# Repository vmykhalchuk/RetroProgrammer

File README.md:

### Ever wondered what happens when my DIY MCU based device:
* after a years of fruitfull work, something bad happens to MCU?
* or this device gets into hands of other DIY electrician for repairing?
- How then shell I find the binary of firmware used in this particular device?
- Is it located on my hard-drive, or on some of backup CDs, or ... baby elephant know where?
- What if I have many devices or single device with many MCUs, each requiring own firmware?
* Now I have to:
 - find required binaries
 - find proper software to upload it over my Programmer
 - make sure MCU model is same, and proper version of firmware is selected

Well, if this ever bothered you - then Retro Programmer is right for you!

## RetroProgrammer
Board for Arduino Nano to convert Arduino into handheld programmer (SD card support, Target IDentification, no PC required, easy to repeat, cheap)

### Idea behind Retro Programmer
 # Short: You want your DIY project to be repairable by any electrician, without skills in MCUs and deep knowledge of your device? Then Retro Programmer is for you!

 # Long story:
You have this device which you will share with others, or make it for your firends or family.
Still you are wandering, what would they do, if it gets broken, MCU in the device sets on fire or anything else happens that will require MCU to be replaced and firmware uploaded?
Without your help - this device is beyound repair, and your friends cannot just ask any electrician to repair it without having skills uploading frimware to your device.

However there is a solution - meet Retro Programmer!

This super-powerefull and low-cost solution will make it super-easy to upload firmware to your device.
* no need to select type of target MCU
* no need to know which firmware has to be uploaded
* no need to use PC
* no need to install uploader software
* no need to search and download your firmware
* no need to make sure many switches are in right position
* Just SINGLE BUTTON operation
* Is not limited to number of MCUs used in your project or projects

All you need is:
* RetroProgrammer Arduino shield
* Arduino Nano or similar
* MicroSD card
* 1-wire ID Tag or set of resistors (one set for every MCU)

### What is Target IDentification (TID for short)
TID is interface with Target Board to Identify program required to upload to MCU.
TID can be of two types:
* Resistive divider - from 4 to 64 TargetIDs supported
* 1wire ID tag - any number of TaregtIDs

Resistive divider can run over Single or Three lines, each representing values from 0 (not connected), 1 to 4.
If single line is used, then only 4 TargetIDs are supported.
If 3 lines are used, then up to 4x4x4=64 TargetIDs are supported.

However in order to support Any number of TargetIDs, the best choice would be 1wire ID tag.

Thanks to TID, Programmer knows what MCU model is expected on Target board and which program to be uploaded.
This eliminates need in searching for a right firmware, and making sure correct MCU is being used.

### Yes I want it!
* DO NOT! UNDER CONSTRUCTION!!! You can order board from here: http://dirtypcbs.com/view.php?share=9566&accesskey=096bf07bd5bc00aa1c8b3e8581d80cb4
* Components - I might share some in very little quantity
* Firmware - pending... draft version see in sources, feel free to contact me (vmykhalchuk_at_gmail_dot_com) for status
* Manual - describes how to use Retro Programmer and how to prepare your project to be supported by Retro Programmer - pending...

### History
When I was developing smart house solution, main concept that I wanted to build into it was - maintainability.
Maintainability is critical factor of having successful system.
It must be easily repairable without special skills needed.
And since Smart House says by itself - it is smart - so it must use a bunch of different microcontroller units.
The problem with MCUs is that to replace such a component on broken board - you need to have a firmware, pc, knowledge on how to upload new firmware.
This dramatically limits a number of electricians who can service your system.

As a solution, I have designed and developed this Handheld programmer shield for Arduino Nano/Micro.

## Main features
* Fully automated, no PC required to operate
* Autodetection of target MCU (ID of target MCU can be autodetected by using extra pin(s) on ICSP). This lets you UPLOAD programm automatically and in one button press.
* Supports AVR microcontrollers (...TBD...)

## Difference between Board v0.1 and v0.2
* v0.2 board has support for Arduino Micro (A4 and A6 are swapped comparing to v0.1 board).
  This gives possibility to support arduino micro for a sake of lost manual programs choices (not possible to select C,D,3,4), only A,B,1,2 will be active.
* Now it also has fixed pinout of ICSP port (mirrored to represent Socket - not Header on Target board).
  This allows user to attach any other Target device with ICSP header directly to Programmer.

## To be implemented
* Add autocalibration routine to calibrate position of DIP switches
 * add same for LEDs and buttons (in case position of buttons was changed)
* Refactor to support Intel HEX files: https://en.wikipedia.org/wiki/Intel_HEX
* Implement preserving of EEPROM memory when requested in HRP file (otherwise it is erased together with Program memory)
* Implement support of Arduino Bootloader (to avoid erasing whole device)
* CRC every HRP file before programming/verifying it!
 * CRC every conf file
* Auto detection of programming speed
* Auto detection of power present on Target device - to avoid turning programming voltage ON
* Support of 3.3v target MCU
 * How to autodetect if this is 3.3v or 5v device?
 * Then we need level shifter to work on two separate supply levels.
  - For this the ideal solution is: 74LVC2T45; 74LVCH2T45
  - Price on Aliexperess is OK for 50pieces only.
  - Or search for “dual supply level” shifter/translator.
* Extend AVR supported list
* Support PDI interface (http://www.atmel.com/images/doc8282.pdf)
* PIC support
* Support 1-wire EEPROM instead of ID (this will let manufacturer to write version of software required to be uploaded, without need to define every single ID).
 * This is more costly then ID device, however gives more flexibility and allows to support many devices of same type
* USB mode 2: Upload directly from manufacturer web-site (will connect to main website where IDs are registered, and will download program specific for given device).
 * 1-wire eeprom would be beneficial here if manufacturer produced many devices which basically require single version of firmware. So manufacturer can register unique device prototype ID which can be stored on eeprom and uploaded to every such eeprom for every similar device. Then such ID can be used to download firmware required.
* USB mode: Upload to Target MCU from Arduino dev environment via USB cable (no SD involved)
* Add support of ZIF sockets
 * can be implemented as a standalone board connected to ICSP+TD socket
 * there can be also additional DIP switches to select program
 * alternatively mcu with 7segment digits and roller to select program, mcu will have to emulate 1wire interface
* Add two 7segment displays, to monitor status and program selected
* Or add LCD display for this
* Add rotary decoder to quickly select manual programm
* Implement Stack-like error handling with arbitrary data supported for debugging

### To be implemented (DONE)
* Support for Arduino Micro - DONE!!! Board since v0.2 supports Arduino Micro or equivalent.
 * software has to be modified slightly
 * pin A4 must be swapped with A6 (Arduino Micro has no A6 nor A7, so we will have limited Manual programs selection)

## Board improvements / fixes
* Add Atmega directly instead of Arduino Board
* Redesign Controls circuits:
  * Put leds on digital pins instead of analogue
  * Put all buttons on single analogue pin
  * this way we still will use three ports, however:
    # there will be no artifact when led slightly lights when button pressed
    # it will be possible to maintain group of leds ON by using PWM, the brightness will stay same
    # or it will be possible to maintain single led on, however it will light brighter
* Swap UPLOAD <=> BACKUP!!!! This is critical, when ERR led is lit - it reads as UPLOAD button is pressed!
  * Check what happens if other combination of LEDs is lit, which button is then assumed as pressed!
* Add jumper to block Manual program selector - when blocked - only Auto TID is expected to work, otherwise failure!
  - this can be easily done by attaching A3 to ground via jumper, then A3 will read 0, which will indicate program to not read Manual program, and rely on Auto selector only.
* Add jumper to block TargetVPP from being supplied by Programmer
  - this is for precaution, when Target board is externally powered
  - easy to implement by removing jumper which connects D3 to transistor base. When connection is broken, transistor will never open to supply TargetVPP.
  - still MCU can monitor if VPP is provided to MCU by reading voltage on ICSP_VPP directly
* Move LEDs to the edge of board, so they are move visible and distinguishable
* Fix TargetVPP - when Arduino board is not connected, or is RESET - TargetVPP is Enabled till MCU gets control over ports. This must be redesigned! Just remove one transistor, thats it.
* Add LED to show that TargetVPP is ON
* Add switch to turn-off power supply to target MCU (in case it uses own power supply)
  * additionally auto-sense voltage on VPP and disable VPP-on switch to prevent failures
  * also add this option into automatic TargetID detection algorithm - to check if it is expected to have VPP on target board or not, and what level of voltage required (5v or 3.3v)
* Add LED to show when SD card bussy (attach to CS pin)

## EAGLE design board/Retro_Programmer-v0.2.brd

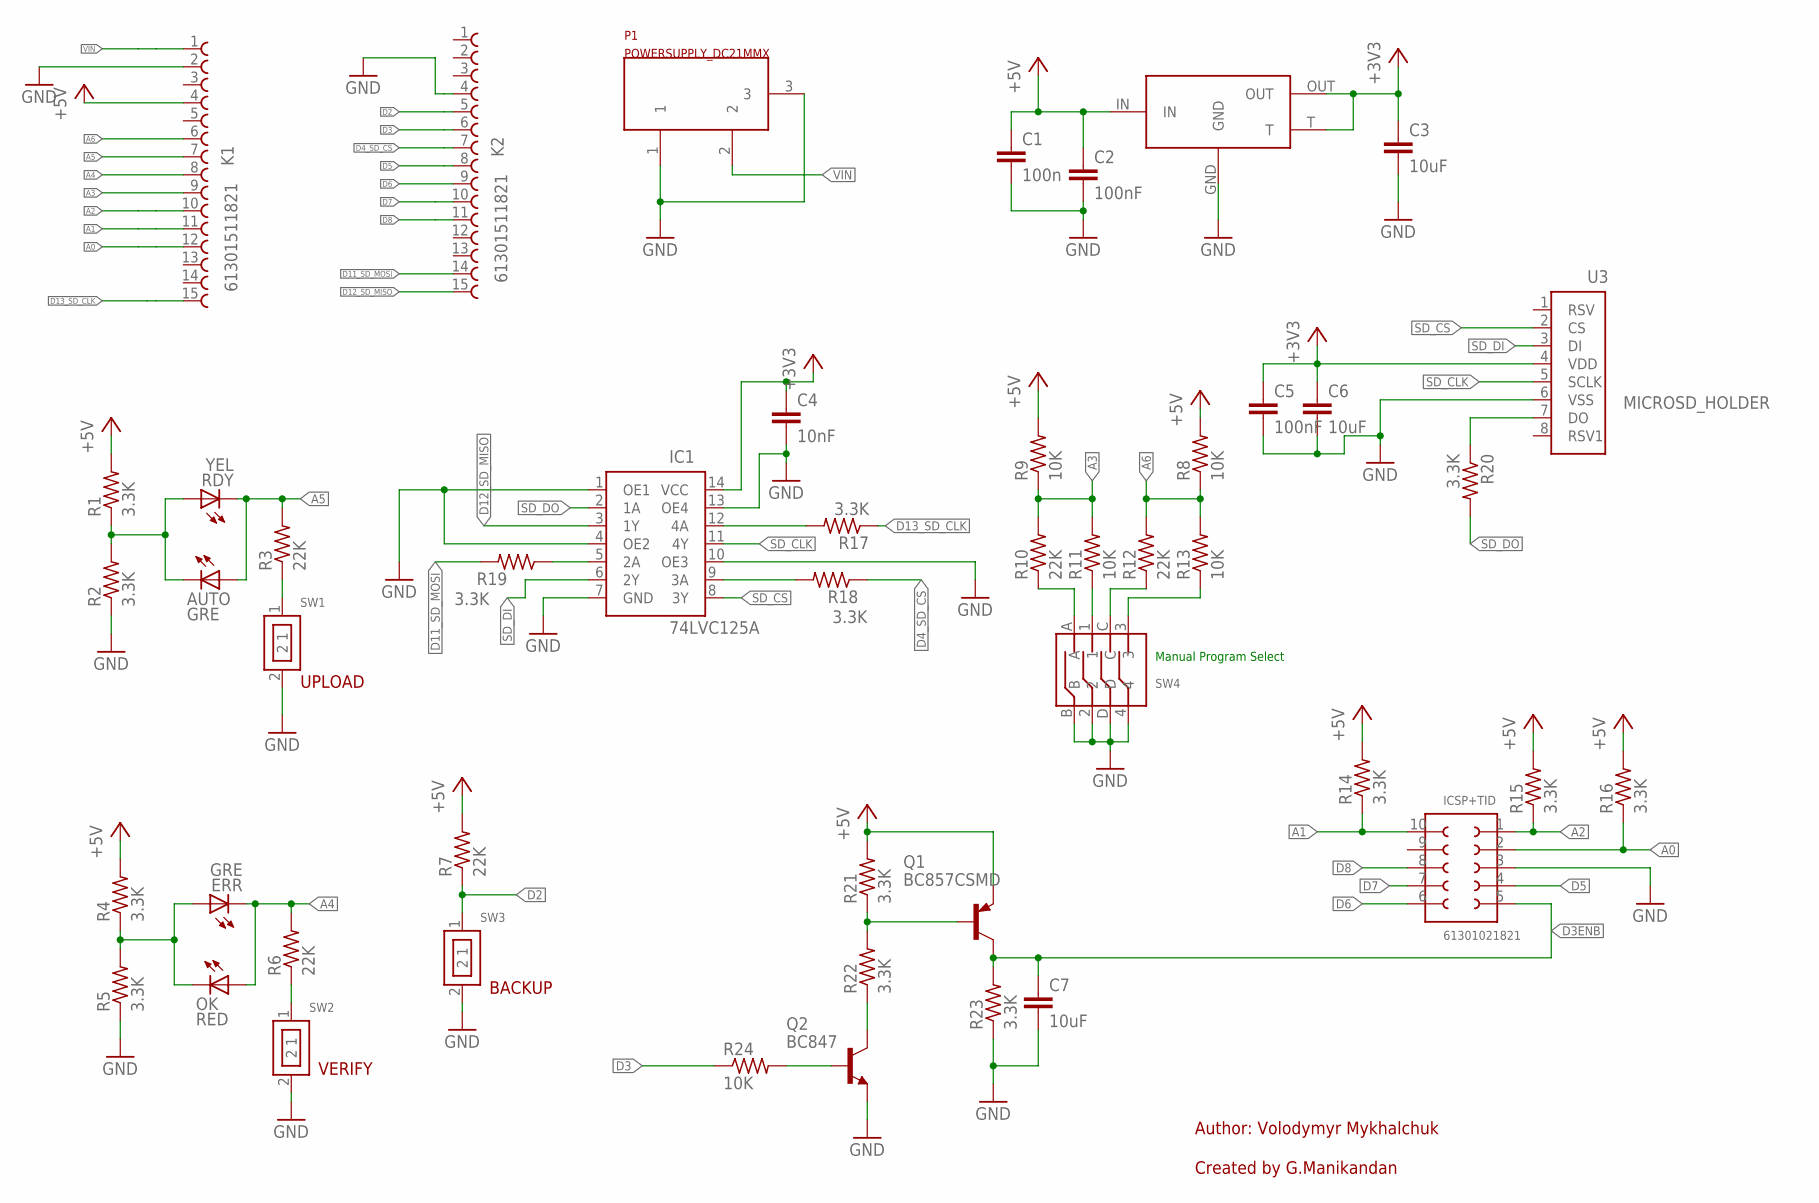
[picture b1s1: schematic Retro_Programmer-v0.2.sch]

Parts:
AUTO: GRE; CHIPLED_1206
C1: 100n; C1206
C2, C5: 100nF; C1206
C3, C6, C7: 10uF; C1206
C4: 10nF; C1206
ERR: GRE; CHIPLED_1206
IC1: 74LVC125A; SOIC14_74L
ICSP+TID: 61301021821
K1, K2: 61301511821
OK: RED; CHIPLED_1206
P1: POWERSUPPLY_DC21MMX; POWERSUPPLY_DC-21MM
Q1: BC857CSMD; SOT23-BEC
Q2: BC847; SOT23
R1, R2, R4, R5, R14, R15, R16, R17, R18, R19, R20, R21, R22, R23: 3.3K; R1206
R3, R6, R7, R10, R12: 22K; R1206
R8, R9, R11, R13, R24: 10K; R1206
RDY: YEL; CHIPLED_1206
SW1, SW2, SW3: SPUSH; SLIDE1
SW4: SLIDE_WAY4; SLIDESWITCH_4
U2: LT1117; SOT223
U3: MICROSD_HOLDER; SDCARD_HOLDER

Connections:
+3V3: C3.1, C4.1, C5.1, C6.1, IC1.14 (VCC), U2.OUT, U2.T, U3.4 (VDD)
+5V: C1.1, C2.1, K1.4, Q1.E, R1.2, R4.2, R7.2, R8.2, R9.2, R14.2, R15.2, R16.2, R21.2, U2.IN
A0: ICSP+TID.2, K1.12, R16.1
A1: ICSP+TID.10, K1.11, R14.1
A2: ICSP+TID.1, K1.10, R15.1
A3: K1.9, R9.1, R10.2, R11.2
A4: ERR.C, K1.8, OK.A, R6.2
A5: AUTO.A, K1.7, R3.2, RDY.C
A6: K1.6, R8.1, R12.2, R13.2
D2: K2.5, R7.1, SW3.1
D3: K2.6, R24.1
D3ENB: C7.1, ICSP+TID.5, Q1.C, R23.2
D4_SD_CS: K2.7, R18.1
D5: ICSP+TID.4, K2.8
D6: ICSP+TID.6, K2.9
D7: ICSP+TID.7, K2.10
D8: ICSP+TID.8, K2.11
D11_SD_MOSI: K2.14, R19.2
D12_SD_MISO: IC1.3 (1Y), K2.15
D13_SD_CLK: K1.15, R17.1
GND: C1.2, C2.2, C3.2, C4.2, C5.2, C6.2, C7.2, IC1.1 (OE1), IC1.4 (OE2), IC1.7 (GND), IC1.10 (OE3), IC1.13 (OE4), ICSP+TID.3, K1.2, K2.4, P1.1, P1.3, Q2.2 (E), R2.1, R5.1, R23.1, SW1.2, SW2.2, SW3.2, SW4.2, SW4.4, SW4.B, SW4.D, U2.GND, U3.6 (VSS)
unnamed: AUTO.C, R1.1, R2.2, RDY.A
unnamed: R3.1, SW1.1
unnamed: ERR.A, OK.C, R4.1, R5.2
unnamed: R6.1, SW2.1
unnamed: R10.1, SW4.A
unnamed: R11.1, SW4.1
unnamed: R12.1, SW4.C
unnamed: R13.1, SW4.3
unnamed: Q1.B, R21.1, R22.2
unnamed: R20.1, U3.7 (DO)
unnamed: Q2.3 (C), R22.1
unnamed: IC1.12 (4A), R17.2
unnamed: IC1.9 (3A), R18.2
unnamed: Q2.1 (B), R24.2
unnamed: IC1.5 (2A), R19.1
SD_CLK: IC1.11 (4Y), U3.5 (SCLK)
SD_CS: IC1.8 (3Y), U3.2 (CS)
SD_DI: IC1.6 (2Y), U3.3 (DI)
SD_DO: IC1.2 (1A), R20.2
VIN: K1.1, P1.2

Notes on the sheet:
UPLOAD
VERIFY
BACKUP
Created by G.Manikandan
Author: Volodymyr Mykhalchuk
Manual Program Select

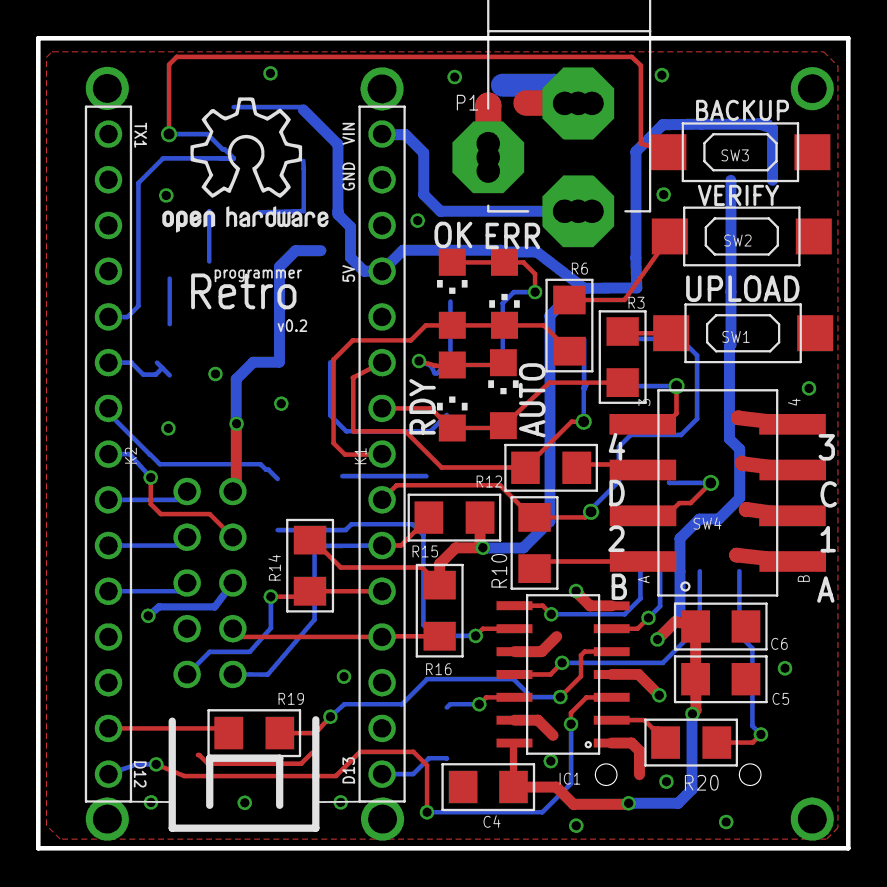
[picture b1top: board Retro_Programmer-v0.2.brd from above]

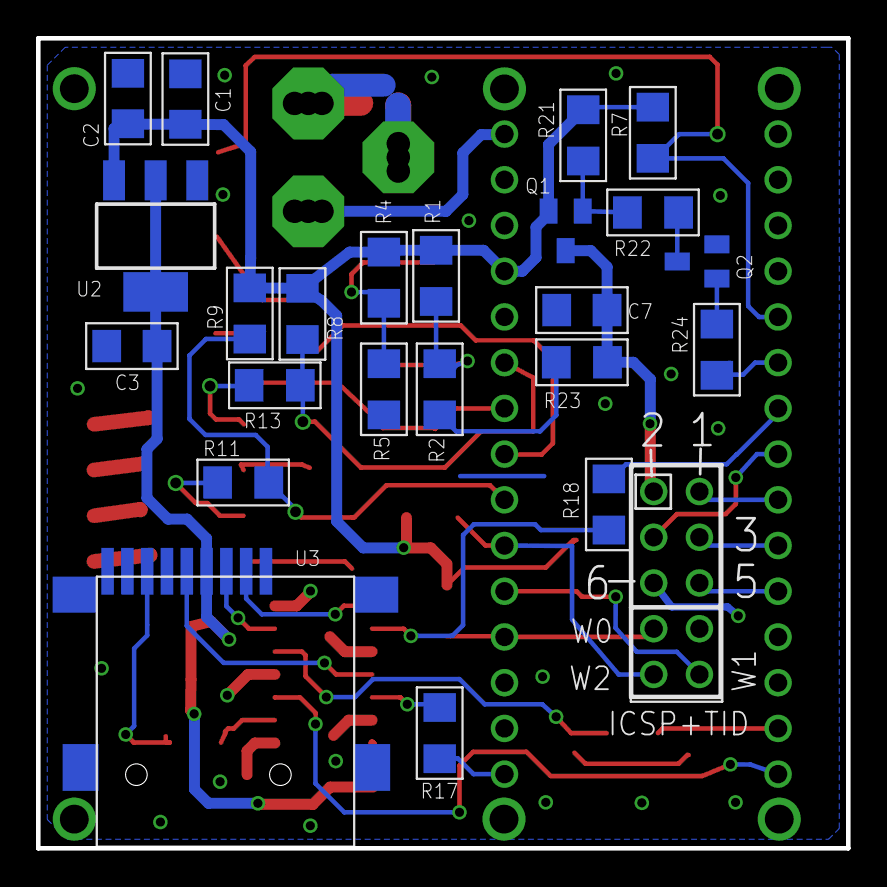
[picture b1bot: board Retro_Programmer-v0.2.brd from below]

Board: 2 copper layers, 45.0 x 45.0 mm, 48 parts (24 on the bottom side), 41 nets.

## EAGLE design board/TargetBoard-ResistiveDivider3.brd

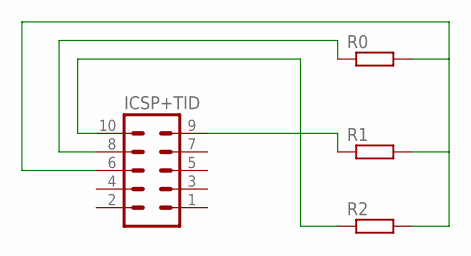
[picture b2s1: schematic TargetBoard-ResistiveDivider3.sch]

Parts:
ICSP+TID: MA05-2
R0, R1, R2: R-EU_R1206; R1206

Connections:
unnamed: ICSP+TID.6, R0.2, R1.2, R2.2
unnamed: ICSP+TID.8, R0.1
unnamed: ICSP+TID.9, R1.1
unnamed: ICSP+TID.10, R2.1

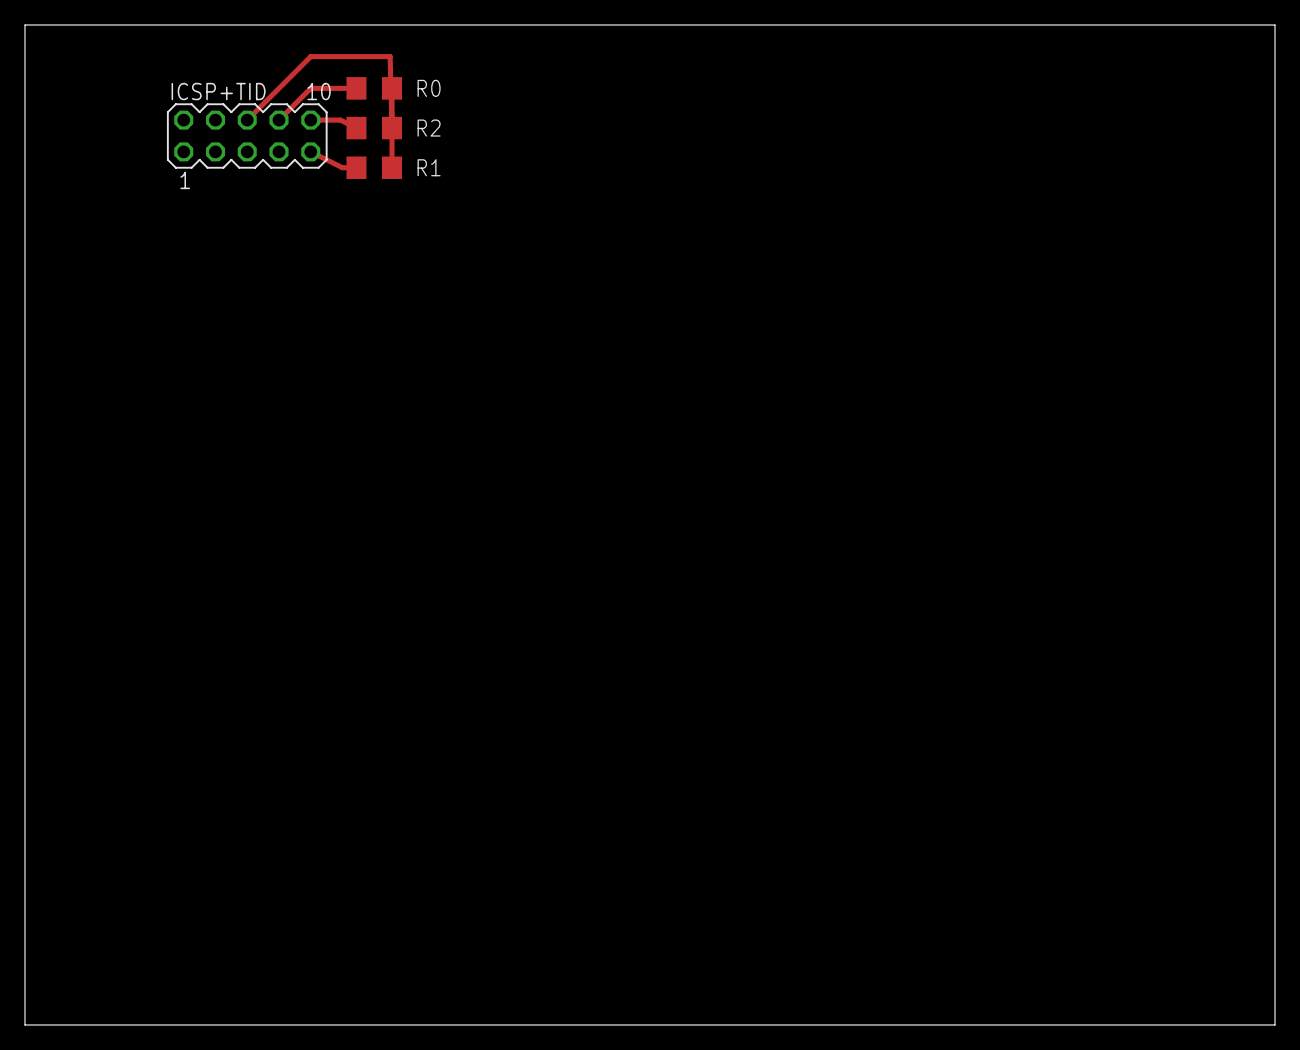
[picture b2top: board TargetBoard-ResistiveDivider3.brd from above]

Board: 2 copper layers, 100.0 x 80.0 mm, 4 parts (0 on the bottom side), 4 nets.

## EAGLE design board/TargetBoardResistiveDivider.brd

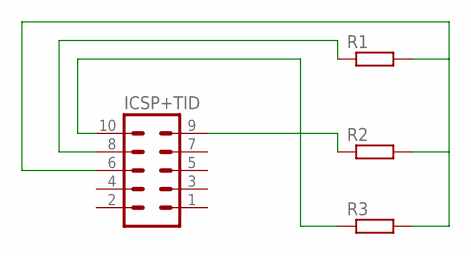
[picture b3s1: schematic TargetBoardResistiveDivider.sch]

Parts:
ICSP+TID: MA05-2
R1, R2, R3: R-EU_R1206; R1206

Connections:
unnamed: ICSP+TID.6, R1.2, R2.2, R3.2
unnamed: ICSP+TID.8, R1.1
unnamed: ICSP+TID.9, R2.1
unnamed: ICSP+TID.10, R3.1

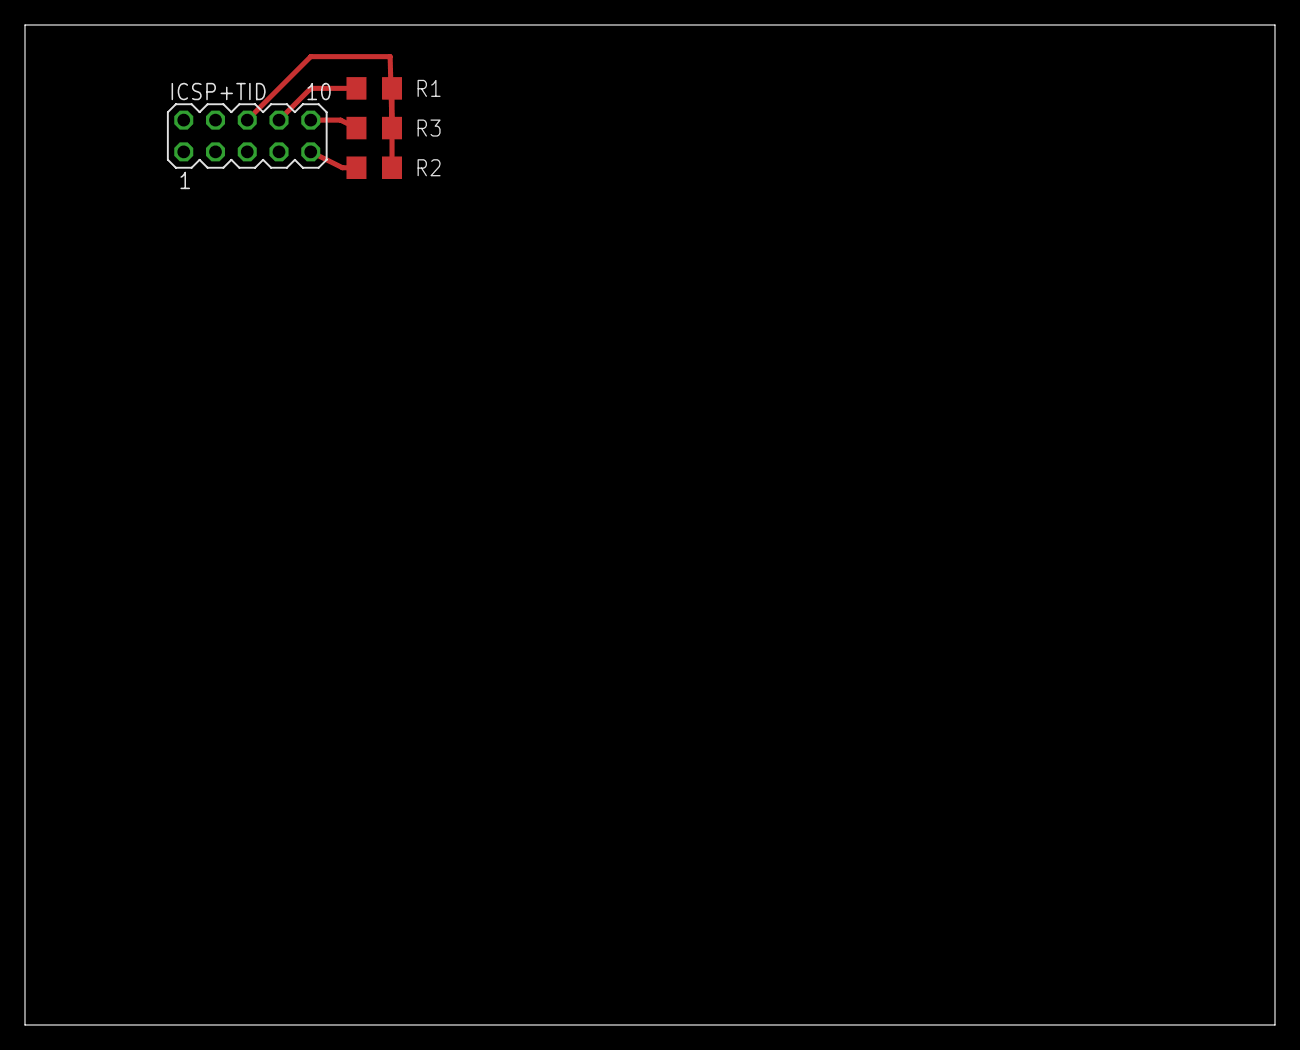
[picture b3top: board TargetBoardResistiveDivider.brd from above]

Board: 2 copper layers, 100.0 x 80.0 mm, 4 parts (0 on the bottom side), 4 nets.

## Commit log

2015-07-19 Initial design ideas + License
2015-07-19 cleanup
2015-07-23 Misc
2015-07-24 new ideas
2015-07-26 Added schematic and board from Manikandan
2015-07-26 improved labelling on board
2015-07-26 font changes
2015-07-27 added gerber files
2015-07-29 More bla bla bla
2015-08-04 Arduino Sketch for Programmer
    Draft version (not working, only tests)
2015-08-04 Added board v0.2
    v0.2 board has support for Arduino Micro (A4 and A6 are swapped
    comparing to v0.1 board) which gives possibility to support arduino
    micro for a sake of lost manual programs choices (not possible to
    select C,D,3,4), only A,B,1,2 will be active.
2015-08-13 lets make some order
2015-08-20 Classes are here
2015-08-20 Its better to use static methods indeed!
    What if we remove classes at all - they seem to use a lot of progmem
    space!
2015-08-20 oh, thats creepy c++
2015-08-20 a bit more
2015-08-31 More separation between test and main code
2015-09-03 Fixed HWInterface; Small fixes
2015-09-03 Mirrored ICSP
2015-09-03 Fixed ground connection to ICSP
2015-09-05 Improved errors handling, Code refactoring, Organised tests
2015-09-05 Board: Fixed ICSP+TID label, and other labels
2015-09-06 Refactoring; Improved error handling
2015-09-06 refactoring
2015-09-11 docs
2015-09-12 board: improved ICSP marking
2015-09-17 Fixed issue with Upload of HRP file
    - fixed by swapping order of Low & High bytes to be loaded
    - swapped low and high in the file - to match low-endian applied in
    Intel HEX (Arduino)
    - small fixes
2015-09-17 Added Target board ICSP+TID examples
2015-09-25 Intel HEX File Parser
    Added parser of Intel HEX file format
2015-09-25 Board v0.2 - corrected DIP labels (code correction required)
2015-09-25 misc ideas
2016-03-21 some temp changes
2019-01-10 Hooray!!!

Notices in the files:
parts and their libraries:
Wuerth_Elektronik_Board_to_Board: Copyright: Würth Elektronik
